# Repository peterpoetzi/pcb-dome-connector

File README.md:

# pcb-dome-connector
A PCB for mechanically connecting wooden geodesic domes

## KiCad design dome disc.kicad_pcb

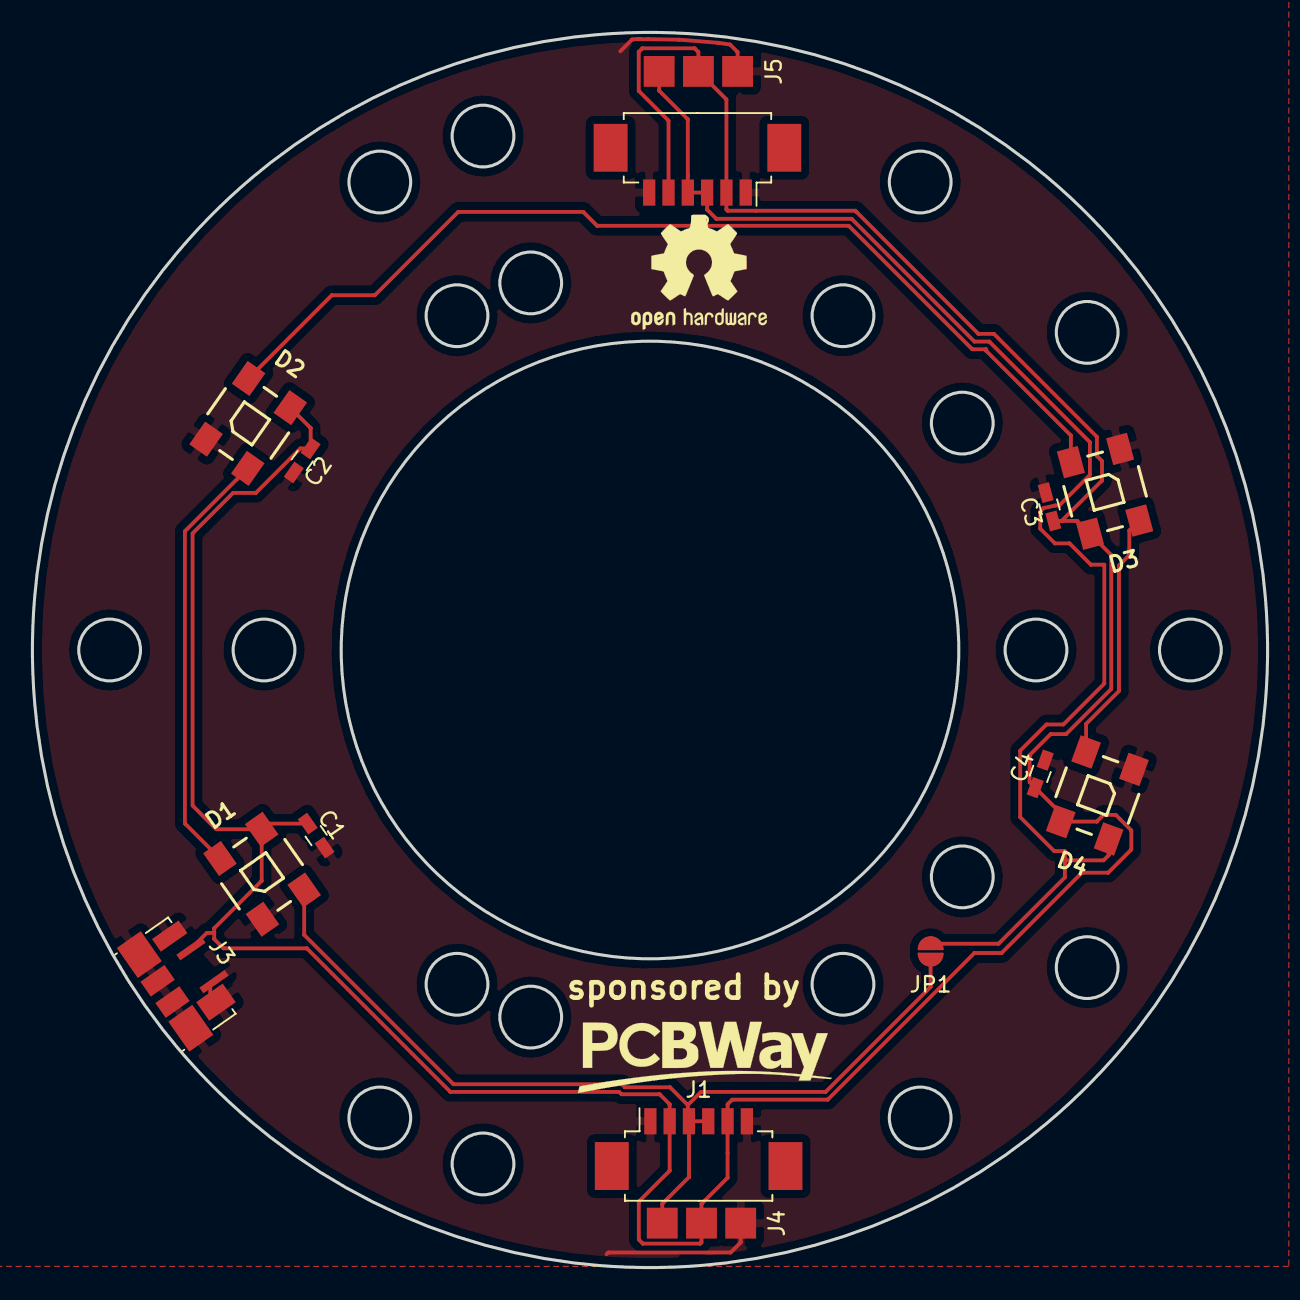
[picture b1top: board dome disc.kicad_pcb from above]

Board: 2 copper layers, 80.0 x 80.0 mm, 14 parts (0 on the bottom side), 7 nets.

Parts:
C1, C2, C3, C4: C; C_0603_HandSoldering
D1, D2, D3, D4: WS2812B
J1, J2: Conn_01x06; Molex_PicoBlade_53261-0671_06x1.25mm_Angled
J3: USB_B_Micro; USB_Micro-B_Molex_47346-0001
J4, J5: Conn_01x03; Pin_Header_Straight_1x03_Pitch2.54mm
JP1: Jumper; JUMPER-SOLDER-SMD

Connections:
DIN: D1.4, J1.3, J1.4, J4.3, JP1.1
DOUT: D4.2, J2.3, J2.4, J5.3, JP1.2
GND: C1.2, C2.2, C3.2, C4.2, D1.3, D2.3, D3.3, D4.3, J1.1, J1.6, J2.1, J2.6, J3.5, J3.6, J4.1, J5.1
unnamed: D1.2, D2.4
unnamed: D2.2, D3.4
unnamed: D3.2, D4.4
VCC: C1.1, C2.1, C3.1, C4.1, D1.1, D2.1, D3.1, D4.1, J1.2, J1.5, J2.2, J2.5, J3.1, J4.2, J5.2

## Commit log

2018-10-24 first version
